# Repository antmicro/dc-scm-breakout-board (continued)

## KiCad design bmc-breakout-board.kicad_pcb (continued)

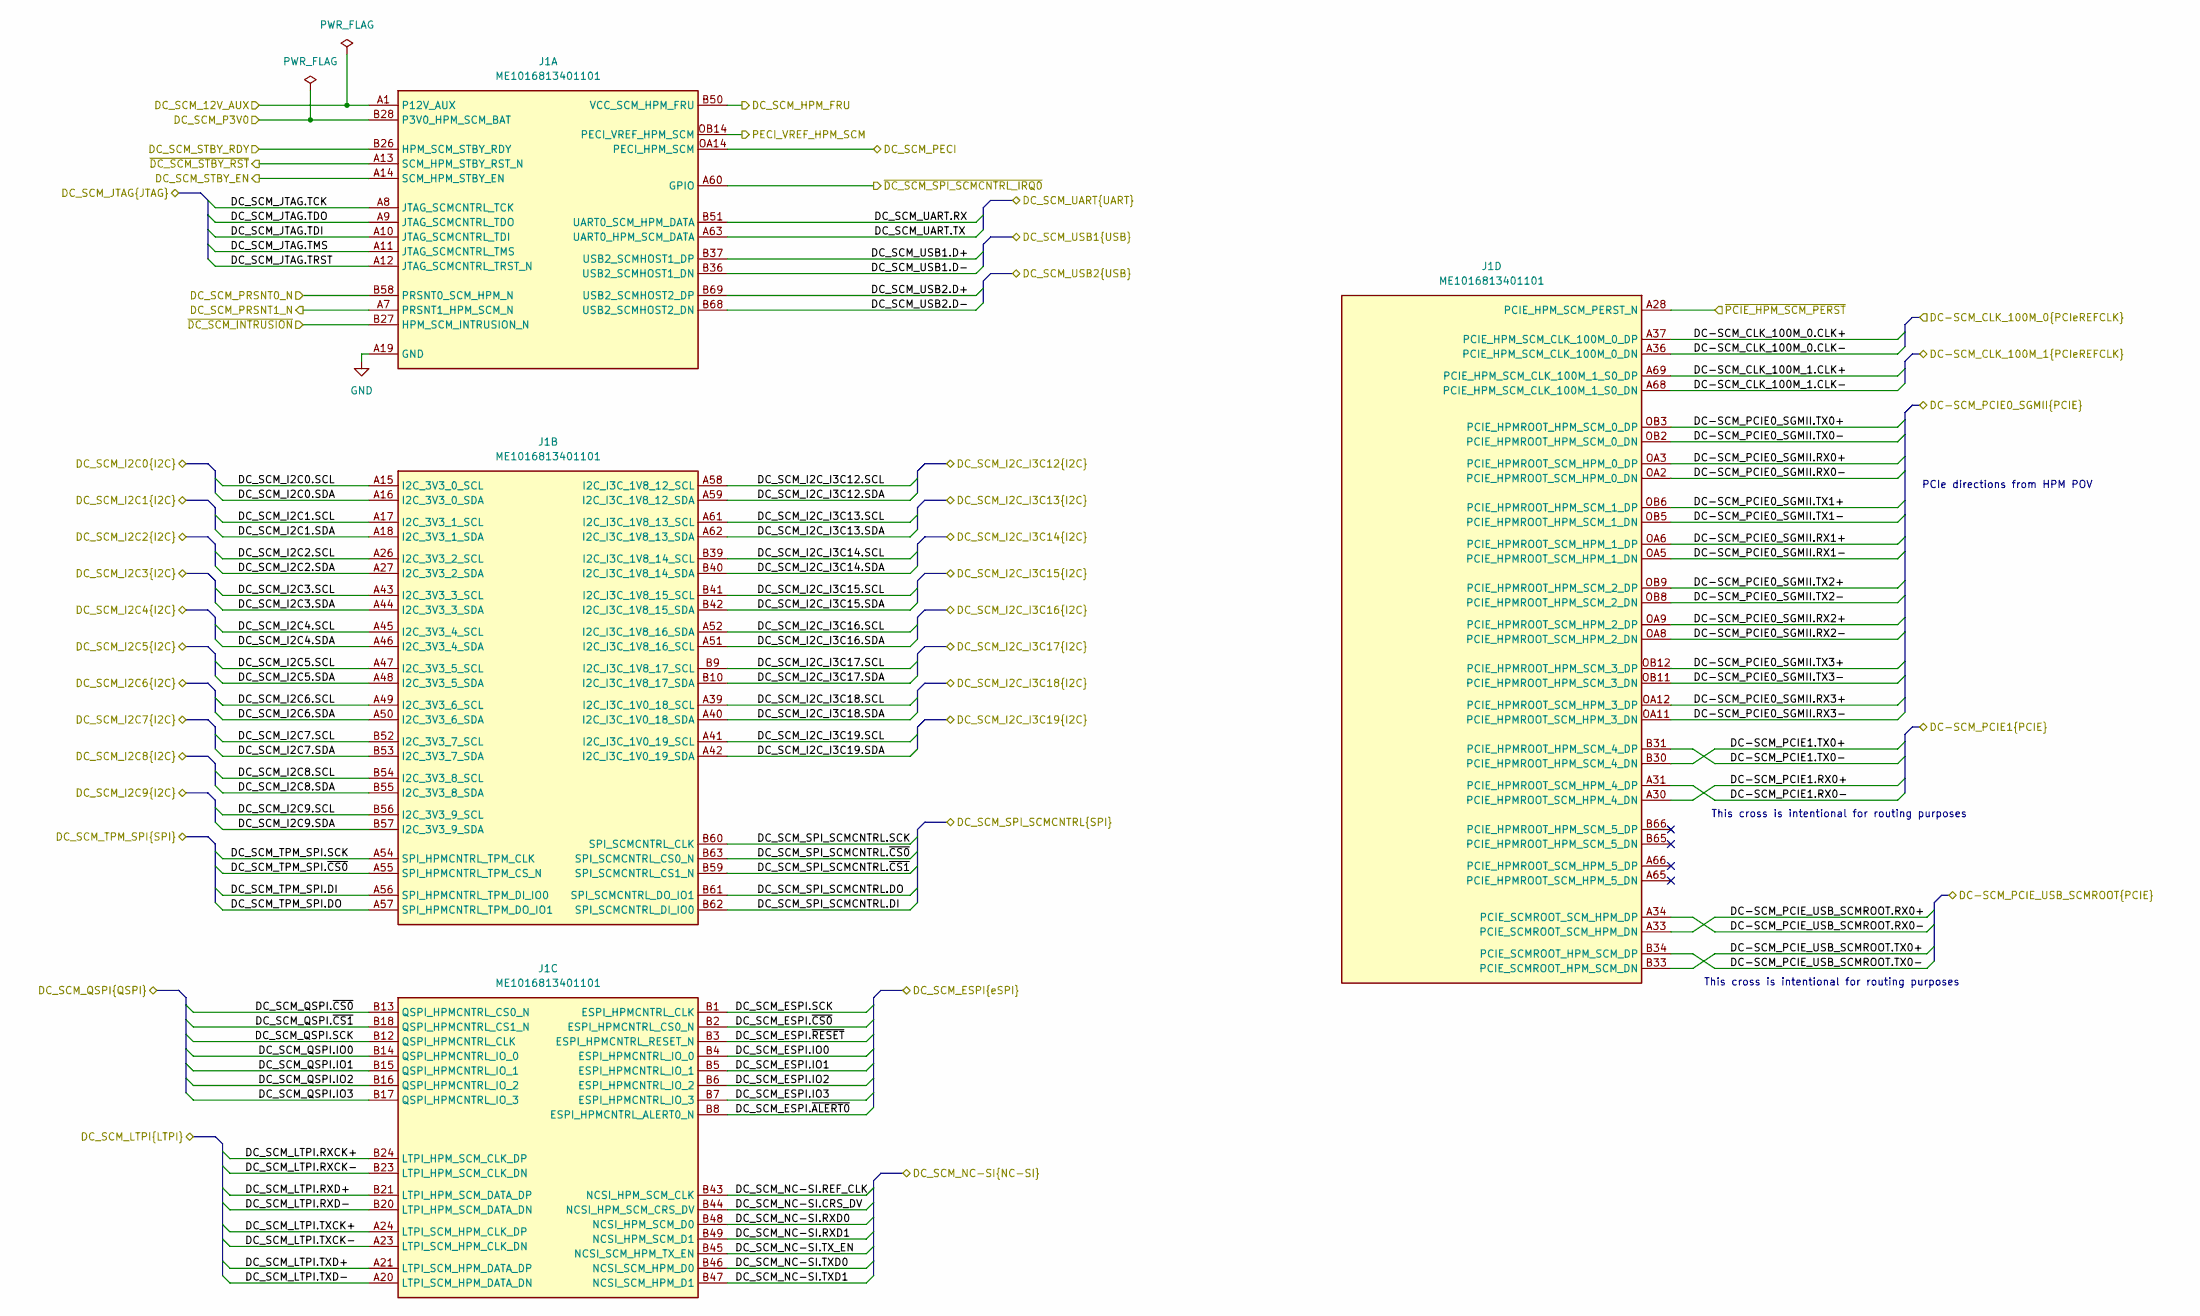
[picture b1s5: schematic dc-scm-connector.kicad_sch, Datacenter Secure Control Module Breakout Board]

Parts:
J1: Socket_DC-SCM-2.1_2x84_Rev-1-1_CUSTOM; Socket_DC-SCM-2.1_2x84_Rev-1-1; MPN ME1016813401101

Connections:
+12V: J1.A1 (P12V_AUX), J1.A2 (P12V_AUX), J1.A3 (P12V_AUX), J1.A4 (P12V_AUX); also elsewhere on the board
/DC-SCM 2.1 connector/DC-SCM_CLK_100M_0.CLK+: J1.A37 (PCIE_HPM_SCM_CLK_100M_0_DP); also elsewhere on the board
/DC-SCM 2.1 connector/DC-SCM_CLK_100M_0.CLK-: J1.A36 (PCIE_HPM_SCM_CLK_100M_0_DN); also elsewhere on the board
/DC-SCM 2.1 connector/DC-SCM_CLK_100M_1.CLK+: J1.A69 (PCIE_HPM_SCM_CLK_100M_1_S0_DP); also elsewhere on the board
/DC-SCM 2.1 connector/DC-SCM_CLK_100M_1.CLK-: J1.A68 (PCIE_HPM_SCM_CLK_100M_1_S0_DN); also elsewhere on the board
/DC-SCM 2.1 connector/DC-SCM_PCIE0_SGMII.RX0+: J1.OA3 (PCIE_HPMROOT_SCM_HPM_0_DP)
/DC-SCM 2.1 connector/DC-SCM_PCIE0_SGMII.RX0-: J1.OA2 (PCIE_HPMROOT_SCM_HPM_0_DN)
/DC-SCM 2.1 connector/DC-SCM_PCIE0_SGMII.RX1+: J1.OA6 (PCIE_HPMROOT_SCM_HPM_1_DP)
/DC-SCM 2.1 connector/DC-SCM_PCIE0_SGMII.RX1-: J1.OA5 (PCIE_HPMROOT_SCM_HPM_1_DN)
/DC-SCM 2.1 connector/DC-SCM_PCIE0_SGMII.RX2+: J1.OA9 (PCIE_HPMROOT_SCM_HPM_2_DP)
/DC-SCM 2.1 connector/DC-SCM_PCIE0_SGMII.RX2-: J1.OA8 (PCIE_HPMROOT_SCM_HPM_2_DN)
/DC-SCM 2.1 connector/DC-SCM_PCIE0_SGMII.RX3+: J1.OA12 (PCIE_HPMROOT_SCM_HPM_3_DP)
/DC-SCM 2.1 connector/DC-SCM_PCIE0_SGMII.RX3-: J1.OA11 (PCIE_HPMROOT_SCM_HPM_3_DN)
/DC-SCM 2.1 connector/DC-SCM_PCIE0_SGMII.TX0+: J1.OB3 (PCIE_HPMROOT_HPM_SCM_0_DP)
/DC-SCM 2.1 connector/DC-SCM_PCIE0_SGMII.TX0-: J1.OB2 (PCIE_HPMROOT_HPM_SCM_0_DN)
/DC-SCM 2.1 connector/DC-SCM_PCIE0_SGMII.TX1+: J1.OB6 (PCIE_HPMROOT_HPM_SCM_1_DP)
/DC-SCM 2.1 connector/DC-SCM_PCIE0_SGMII.TX1-: J1.OB5 (PCIE_HPMROOT_HPM_SCM_1_DN)
/DC-SCM 2.1 connector/DC-SCM_PCIE0_SGMII.TX2+: J1.OB9 (PCIE_HPMROOT_HPM_SCM_2_DP)
/DC-SCM 2.1 connector/DC-SCM_PCIE0_SGMII.TX2-: J1.OB8 (PCIE_HPMROOT_HPM_SCM_2_DN)
/DC-SCM 2.1 connector/DC-SCM_PCIE0_SGMII.TX3+: J1.OB12 (PCIE_HPMROOT_HPM_SCM_3_DP)
/DC-SCM 2.1 connector/DC-SCM_PCIE0_SGMII.TX3-: J1.OB11 (PCIE_HPMROOT_HPM_SCM_3_DN)
/DC-SCM 2.1 connector/DC-SCM_PCIE1.RX0+: J1.A30 (PCIE_HPMROOT_SCM_HPM_4_DN); also elsewhere on the board
/DC-SCM 2.1 connector/DC-SCM_PCIE1.RX0-: J1.A31 (PCIE_HPMROOT_SCM_HPM_4_DP); also elsewhere on the board
/DC-SCM 2.1 connector/DC-SCM_PCIE1.TX0+: J1.B30 (PCIE_HPMROOT_HPM_SCM_4_DN); also elsewhere on the board
/DC-SCM 2.1 connector/DC-SCM_PCIE1.TX0-: J1.B31 (PCIE_HPMROOT_HPM_SCM_4_DP); also elsewhere on the board
/DC-SCM 2.1 connector/DC-SCM_PCIE_USB_SCMROOT.RX0+: J1.A33 (PCIE_SCMROOT_SCM_HPM_DN); also elsewhere on the board
/DC-SCM 2.1 connector/DC-SCM_PCIE_USB_SCMROOT.RX0-: J1.A34 (PCIE_SCMROOT_SCM_HPM_DP); also elsewhere on the board
/DC-SCM 2.1 connector/DC-SCM_PCIE_USB_SCMROOT.TX0+: J1.B33 (PCIE_SCMROOT_HPM_SCM_DN); also elsewhere on the board
/DC-SCM 2.1 connector/DC-SCM_PCIE_USB_SCMROOT.TX0-: J1.B34 (PCIE_SCMROOT_HPM_SCM_DP); also elsewhere on the board
/DC-SCM 2.1 connector/DC_SCM_ESPI.IO0: J1.B4 (ESPI_HPMCNTRL_IO_0); also elsewhere on the board
/DC-SCM 2.1 connector/DC_SCM_ESPI.IO1: J1.B5 (ESPI_HPMCNTRL_IO_1); also elsewhere on the board
/DC-SCM 2.1 connector/DC_SCM_ESPI.IO2: J1.B6 (ESPI_HPMCNTRL_IO_2); also elsewhere on the board
/DC-SCM 2.1 connector/DC_SCM_ESPI.IO3: J1.B7 (ESPI_HPMCNTRL_IO_3); also elsewhere on the board
/DC-SCM 2.1 connector/DC_SCM_ESPI.SCK: J1.B1 (ESPI_HPMCNTRL_CLK); also elsewhere on the board
/DC-SCM 2.1 connector/DC_SCM_ESPI.~ALERT0: J1.B8 (ESPI_HPMCNTRL_ALERT0_N); also elsewhere on the board
/DC-SCM 2.1 connector/DC_SCM_ESPI.~CS0: J1.B2 (ESPI_HPMCNTRL_CS0_N); also elsewhere on the board
/DC-SCM 2.1 connector/DC_SCM_ESPI.~RESET: J1.B3 (ESPI_HPMCNTRL_RESET_N); also elsewhere on the board
/DC-SCM 2.1 connector/DC_SCM_HPM_FRU: J1.B50 (VCC_SCM_HPM_FRU); also elsewhere on the board
/DC-SCM 2.1 connector/DC_SCM_I2C0.SCL: J1.A15 (I2C_3V3_0_SCL); also elsewhere on the board
/DC-SCM 2.1 connector/DC_SCM_I2C0.SDA: J1.A16 (I2C_3V3_0_SDA); also elsewhere on the board
/DC-SCM 2.1 connector/DC_SCM_I2C1.SCL: J1.A17 (I2C_3V3_1_SCL); also elsewhere on the board
/DC-SCM 2.1 connector/DC_SCM_I2C1.SDA: J1.A18 (I2C_3V3_1_SDA); also elsewhere on the board
/DC-SCM 2.1 connector/DC_SCM_I2C2.SCL: J1.A26 (I2C_3V3_2_SCL); also elsewhere on the board
/DC-SCM 2.1 connector/DC_SCM_I2C2.SDA: J1.A27 (I2C_3V3_2_SDA); also elsewhere on the board
/DC-SCM 2.1 connector/DC_SCM_I2C3.SCL: J1.A43 (I2C_3V3_3_SCL); also elsewhere on the board
/DC-SCM 2.1 connector/DC_SCM_I2C3.SDA: J1.A44 (I2C_3V3_3_SDA); also elsewhere on the board
/DC-SCM 2.1 connector/DC_SCM_I2C4.SCL: J1.A45 (I2C_3V3_4_SCL); also elsewhere on the board
/DC-SCM 2.1 connector/DC_SCM_I2C4.SDA: J1.A46 (I2C_3V3_4_SDA); also elsewhere on the board
/DC-SCM 2.1 connector/DC_SCM_I2C5.SCL: J1.A47 (I2C_3V3_5_SCL); also elsewhere on the board
/DC-SCM 2.1 connector/DC_SCM_I2C5.SDA: J1.A48 (I2C_3V3_5_SDA); also elsewhere on the board
/DC-SCM 2.1 connector/DC_SCM_I2C6.SCL: J1.A49 (I2C_3V3_6_SCL); also elsewhere on the board
/DC-SCM 2.1 connector/DC_SCM_I2C6.SDA: J1.A50 (I2C_3V3_6_SDA); also elsewhere on the board
/DC-SCM 2.1 connector/DC_SCM_I2C7.SCL: J1.B52 (I2C_3V3_7_SCL); also elsewhere on the board
/DC-SCM 2.1 connector/DC_SCM_I2C7.SDA: J1.B53 (I2C_3V3_7_SDA); also elsewhere on the board
/DC-SCM 2.1 connector/DC_SCM_I2C8.SCL: J1.B54 (I2C_3V3_8_SCL); also elsewhere on the board
/DC-SCM 2.1 connector/DC_SCM_I2C8.SDA: J1.B55 (I2C_3V3_8_SDA); also elsewhere on the board
/DC-SCM 2.1 connector/DC_SCM_I2C9.SCL: J1.B56 (I2C_3V3_9_SCL); also elsewhere on the board
/DC-SCM 2.1 connector/DC_SCM_I2C9.SDA: J1.B57 (I2C_3V3_9_SDA); also elsewhere on the board
/DC-SCM 2.1 connector/DC_SCM_I2C_I3C12.SCL: J1.A58 (I2C_I3C_1V8_12_SCL); also elsewhere on the board
/DC-SCM 2.1 connector/DC_SCM_I2C_I3C12.SDA: J1.A59 (I2C_I3C_1V8_12_SDA); also elsewhere on the board
/DC-SCM 2.1 connector/DC_SCM_I2C_I3C13.SCL: J1.A61 (I2C_I3C_1V8_13_SCL); also elsewhere on the board
/DC-SCM 2.1 connector/DC_SCM_I2C_I3C13.SDA: J1.A62 (I2C_I3C_1V8_13_SDA); also elsewhere on the board
/DC-SCM 2.1 connector/DC_SCM_I2C_I3C14.SCL: J1.B39 (I2C_I3C_1V8_14_SCL); also elsewhere on the board
/DC-SCM 2.1 connector/DC_SCM_I2C_I3C14.SDA: J1.B40 (I2C_I3C_1V8_14_SDA); also elsewhere on the board
/DC-SCM 2.1 connector/DC_SCM_I2C_I3C15.SCL: J1.B41 (I2C_I3C_1V8_15_SCL); also elsewhere on the board
/DC-SCM 2.1 connector/DC_SCM_I2C_I3C15.SDA: J1.B42 (I2C_I3C_1V8_15_SDA); also elsewhere on the board
/DC-SCM 2.1 connector/DC_SCM_I2C_I3C16.SCL: J1.A52 (I2C_I3C_1V8_16_SDA); also elsewhere on the board
/DC-SCM 2.1 connector/DC_SCM_I2C_I3C16.SDA: J1.A51 (I2C_I3C_1V8_16_SCL); also elsewhere on the board
/DC-SCM 2.1 connector/DC_SCM_I2C_I3C17.SCL: J1.B9 (I2C_I3C_1V8_17_SCL); also elsewhere on the board
/DC-SCM 2.1 connector/DC_SCM_I2C_I3C17.SDA: J1.B10 (I2C_I3C_1V8_17_SDA); also elsewhere on the board
/DC-SCM 2.1 connector/DC_SCM_I2C_I3C18.SCL: J1.A39 (I2C_I3C_1V0_18_SCL); also elsewhere on the board
/DC-SCM 2.1 connector/DC_SCM_I2C_I3C18.SDA: J1.A40 (I2C_I3C_1V0_18_SDA); also elsewhere on the board
/DC-SCM 2.1 connector/DC_SCM_I2C_I3C19.SCL: J1.A41 (I2C_I3C_1V0_19_SCL); also elsewhere on the board
/DC-SCM 2.1 connector/DC_SCM_I2C_I3C19.SDA: J1.A42 (I2C_I3C_1V0_19_SDA); also elsewhere on the board
/DC-SCM 2.1 connector/DC_SCM_JTAG.TCK: J1.A8 (JTAG_SCMCNTRL_TCK); also elsewhere on the board
/DC-SCM 2.1 connector/DC_SCM_JTAG.TDI: J1.A10 (JTAG_SCMCNTRL_TDI); also elsewhere on the board
/DC-SCM 2.1 connector/DC_SCM_JTAG.TDO: J1.A9 (JTAG_SCMCNTRL_TDO); also elsewhere on the board
/DC-SCM 2.1 connector/DC_SCM_JTAG.TMS: J1.A11 (JTAG_SCMCNTRL_TMS); also elsewhere on the board
/DC-SCM 2.1 connector/DC_SCM_JTAG.TRST: J1.A12 (JTAG_SCMCNTRL_TRST_N); also elsewhere on the board
/DC-SCM 2.1 connector/DC_SCM_LTPI.RXCK+: J1.B24 (LTPI_HPM_SCM_CLK_DP); also elsewhere on the board
/DC-SCM 2.1 connector/DC_SCM_LTPI.RXCK-: J1.B23 (LTPI_HPM_SCM_CLK_DN); also elsewhere on the board
/DC-SCM 2.1 connector/DC_SCM_LTPI.RXD+: J1.B21 (LTPI_HPM_SCM_DATA_DP); also elsewhere on the board
/DC-SCM 2.1 connector/DC_SCM_LTPI.RXD-: J1.B20 (LTPI_HPM_SCM_DATA_DN); also elsewhere on the board
/DC-SCM 2.1 connector/DC_SCM_LTPI.TXCK+: J1.A24 (LTPI_SCM_HPM_CLK_DP); also elsewhere on the board
/DC-SCM 2.1 connector/DC_SCM_LTPI.TXCK-: J1.A23 (LTPI_SCM_HPM_CLK_DN); also elsewhere on the board
/DC-SCM 2.1 connector/DC_SCM_LTPI.TXD+: J1.A21 (LTPI_SCM_HPM_DATA_DP); also elsewhere on the board
/DC-SCM 2.1 connector/DC_SCM_LTPI.TXD-: J1.A20 (LTPI_SCM_HPM_DATA_DN); also elsewhere on the board
/DC-SCM 2.1 connector/DC_SCM_NC-SI.CRS_DV: J1.B44 (NCSI_HPM_SCM_CRS_DV); also elsewhere on the board
/DC-SCM 2.1 connector/DC_SCM_NC-SI.REF_CLK: J1.B43 (NCSI_HPM_SCM_CLK); also elsewhere on the board
/DC-SCM 2.1 connector/DC_SCM_NC-SI.RXD0: J1.B48 (NCSI_HPM_SCM_D0); also elsewhere on the board
/DC-SCM 2.1 connector/DC_SCM_NC-SI.RXD1: J1.B49 (NCSI_HPM_SCM_D1); also elsewhere on the board
/DC-SCM 2.1 connector/DC_SCM_NC-SI.TXD0: J1.B46 (NCSI_SCM_HPM_D0); also elsewhere on the board
/DC-SCM 2.1 connector/DC_SCM_NC-SI.TXD1: J1.B47 (NCSI_SCM_HPM_D1); also elsewhere on the board
/DC-SCM 2.1 connector/DC_SCM_NC-SI.TX_EN: J1.B45 (NCSI_SCM_HPM_TX_EN); also elsewhere on the board
/DC-SCM 2.1 connector/DC_SCM_P3V0: J1.B28 (P3V0_HPM_SCM_BAT); also elsewhere on the board
/DC-SCM 2.1 connector/DC_SCM_PECI: J1.OA14 (PECI_HPM_SCM); also elsewhere on the board
/DC-SCM 2.1 connector/DC_SCM_PRSNT0_N: J1.B58 (PRSNT0_SCM_HPM_N); also elsewhere on the board
/DC-SCM 2.1 connector/DC_SCM_PRSNT1_N: J1.A7 (PRSNT1_HPM_SCM_N); also elsewhere on the board
/DC-SCM 2.1 connector/DC_SCM_QSPI.IO0: J1.B14 (QSPI_HPMCNTRL_IO_0); also elsewhere on the board
/DC-SCM 2.1 connector/DC_SCM_QSPI.IO1: J1.B15 (QSPI_HPMCNTRL_IO_1); also elsewhere on the board
/DC-SCM 2.1 connector/DC_SCM_QSPI.IO2: J1.B16 (QSPI_HPMCNTRL_IO_2); also elsewhere on the board
/DC-SCM 2.1 connector/DC_SCM_QSPI.IO3: J1.B17 (QSPI_HPMCNTRL_IO_3); also elsewhere on the board
/DC-SCM 2.1 connector/DC_SCM_QSPI.SCK: J1.B12 (QSPI_HPMCNTRL_CLK); also elsewhere on the board
/DC-SCM 2.1 connector/DC_SCM_QSPI.~CS0: J1.B13 (QSPI_HPMCNTRL_CS0_N); also elsewhere on the board
/DC-SCM 2.1 connector/DC_SCM_QSPI.~CS1: J1.B18 (QSPI_HPMCNTRL_CS1_N); also elsewhere on the board
/DC-SCM 2.1 connector/DC_SCM_SPI_SCMCNTRL.DI: J1.B62 (SPI_SCMCNTRL_DI_IO0); also elsewhere on the board
/DC-SCM 2.1 connector/DC_SCM_SPI_SCMCNTRL.DO: J1.B61 (SPI_SCMCNTRL_DO_IO1); also elsewhere on the board
/DC-SCM 2.1 connector/DC_SCM_SPI_SCMCNTRL.SCK: J1.B60 (SPI_SCMCNTRL_CLK); also elsewhere on the board
/DC-SCM 2.1 connector/DC_SCM_SPI_SCMCNTRL.~CS0: J1.B63 (SPI_SCMCNTRL_CS0_N); also elsewhere on the board
/DC-SCM 2.1 connector/DC_SCM_SPI_SCMCNTRL.~CS1: J1.B59 (SPI_SCMCNTRL_CS1_N); also elsewhere on the board
/DC-SCM 2.1 connector/DC_SCM_STBY_EN: J1.A14 (SCM_HPM_STBY_EN); also elsewhere on the board
/DC-SCM 2.1 connector/DC_SCM_STBY_RDY: J1.B26 (HPM_SCM_STBY_RDY); also elsewhere on the board
/DC-SCM 2.1 connector/DC_SCM_TPM_SPI.DI: J1.A56 (SPI_HPMCNTRL_TPM_DI_IO0); also elsewhere on the board
/DC-SCM 2.1 connector/DC_SCM_TPM_SPI.DO: J1.A57 (SPI_HPMCNTRL_TPM_DO_IO1); also elsewhere on the board
/DC-SCM 2.1 connector/DC_SCM_TPM_SPI.SCK: J1.A54 (SPI_HPMCNTRL_TPM_CLK); also elsewhere on the board
/DC-SCM 2.1 connector/DC_SCM_TPM_SPI.~CS0: J1.A55 (SPI_HPMCNTRL_TPM_CS_N); also elsewhere on the board
/DC-SCM 2.1 connector/DC_SCM_UART.RX: J1.B51 (UART0_SCM_HPM_DATA); also elsewhere on the board
/DC-SCM 2.1 connector/DC_SCM_UART.TX: J1.A63 (UART0_HPM_SCM_DATA); also elsewhere on the board
/DC-SCM 2.1 connector/DC_SCM_USB1.D+: J1.B37 (USB2_SCMHOST1_DP); also elsewhere on the board
/DC-SCM 2.1 connector/DC_SCM_USB1.D-: J1.B36 (USB2_SCMHOST1_DN); also elsewhere on the board
/DC-SCM 2.1 connector/DC_SCM_USB2.D+: J1.B69 (USB2_SCMHOST2_DP); also elsewhere on the board
/DC-SCM 2.1 connector/DC_SCM_USB2.D-: J1.B68 (USB2_SCMHOST2_DN); also elsewhere on the board
/DC-SCM 2.1 connector/PECI_VREF_HPM_SCM: J1.OB14 (PECI_VREF_HPM_SCM); also elsewhere on the board
/DC-SCM 2.1 connector/~DC_SCM_INTRUSION: J1.B27 (HPM_SCM_INTRUSION_N); also elsewhere on the board
/DC-SCM 2.1 connector/~DC_SCM_SPI_SCMCNTRL_IRQ0: J1.A60 (GPIO); also elsewhere on the board
/DC-SCM 2.1 connector/~DC_SCM_STBY_RST: J1.A13 (SCM_HPM_STBY_RST_N); also elsewhere on the board
/DC-SCM 2.1 connector/~PCIE_HPM_SCM_PERST: J1.A28 (PCIE_HPM_SCM_PERST_N); also elsewhere on the board
GND: J1.A5 (GND), J1.A6 (GND), J1.A19 (GND), J1.A22 (GND), J1.A25 (GND), J1.A29 (GND), J1.A32 (GND), J1.A35 (GND), J1.A38 (GND), J1.A53 (GND), J1.A64 (GND), J1.A67 (GND), J1.A70 (GND), J1.B11 (GND), J1.B19 (GND), J1.B22 (GND), J1.B25 (GND), J1.B29 (GND), J1.B32 (GND), J1.B35 (GND), J1.B38 (GND), J1.B64 (GND), J1.B67 (GND), J1.B70 (GND), J1.OA1 (GND), J1.OA4 (GND), J1.OA7 (GND), J1.OA10 (GND), J1.OA13 (GND), J1.OB1 (GND), J1.OB4 (GND), J1.OB7 (GND), J1.OB10 (GND), J1.OB13 (GND); also elsewhere on the board

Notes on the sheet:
PCIe directions from HPM POV
This cross is intentional for routing purposes

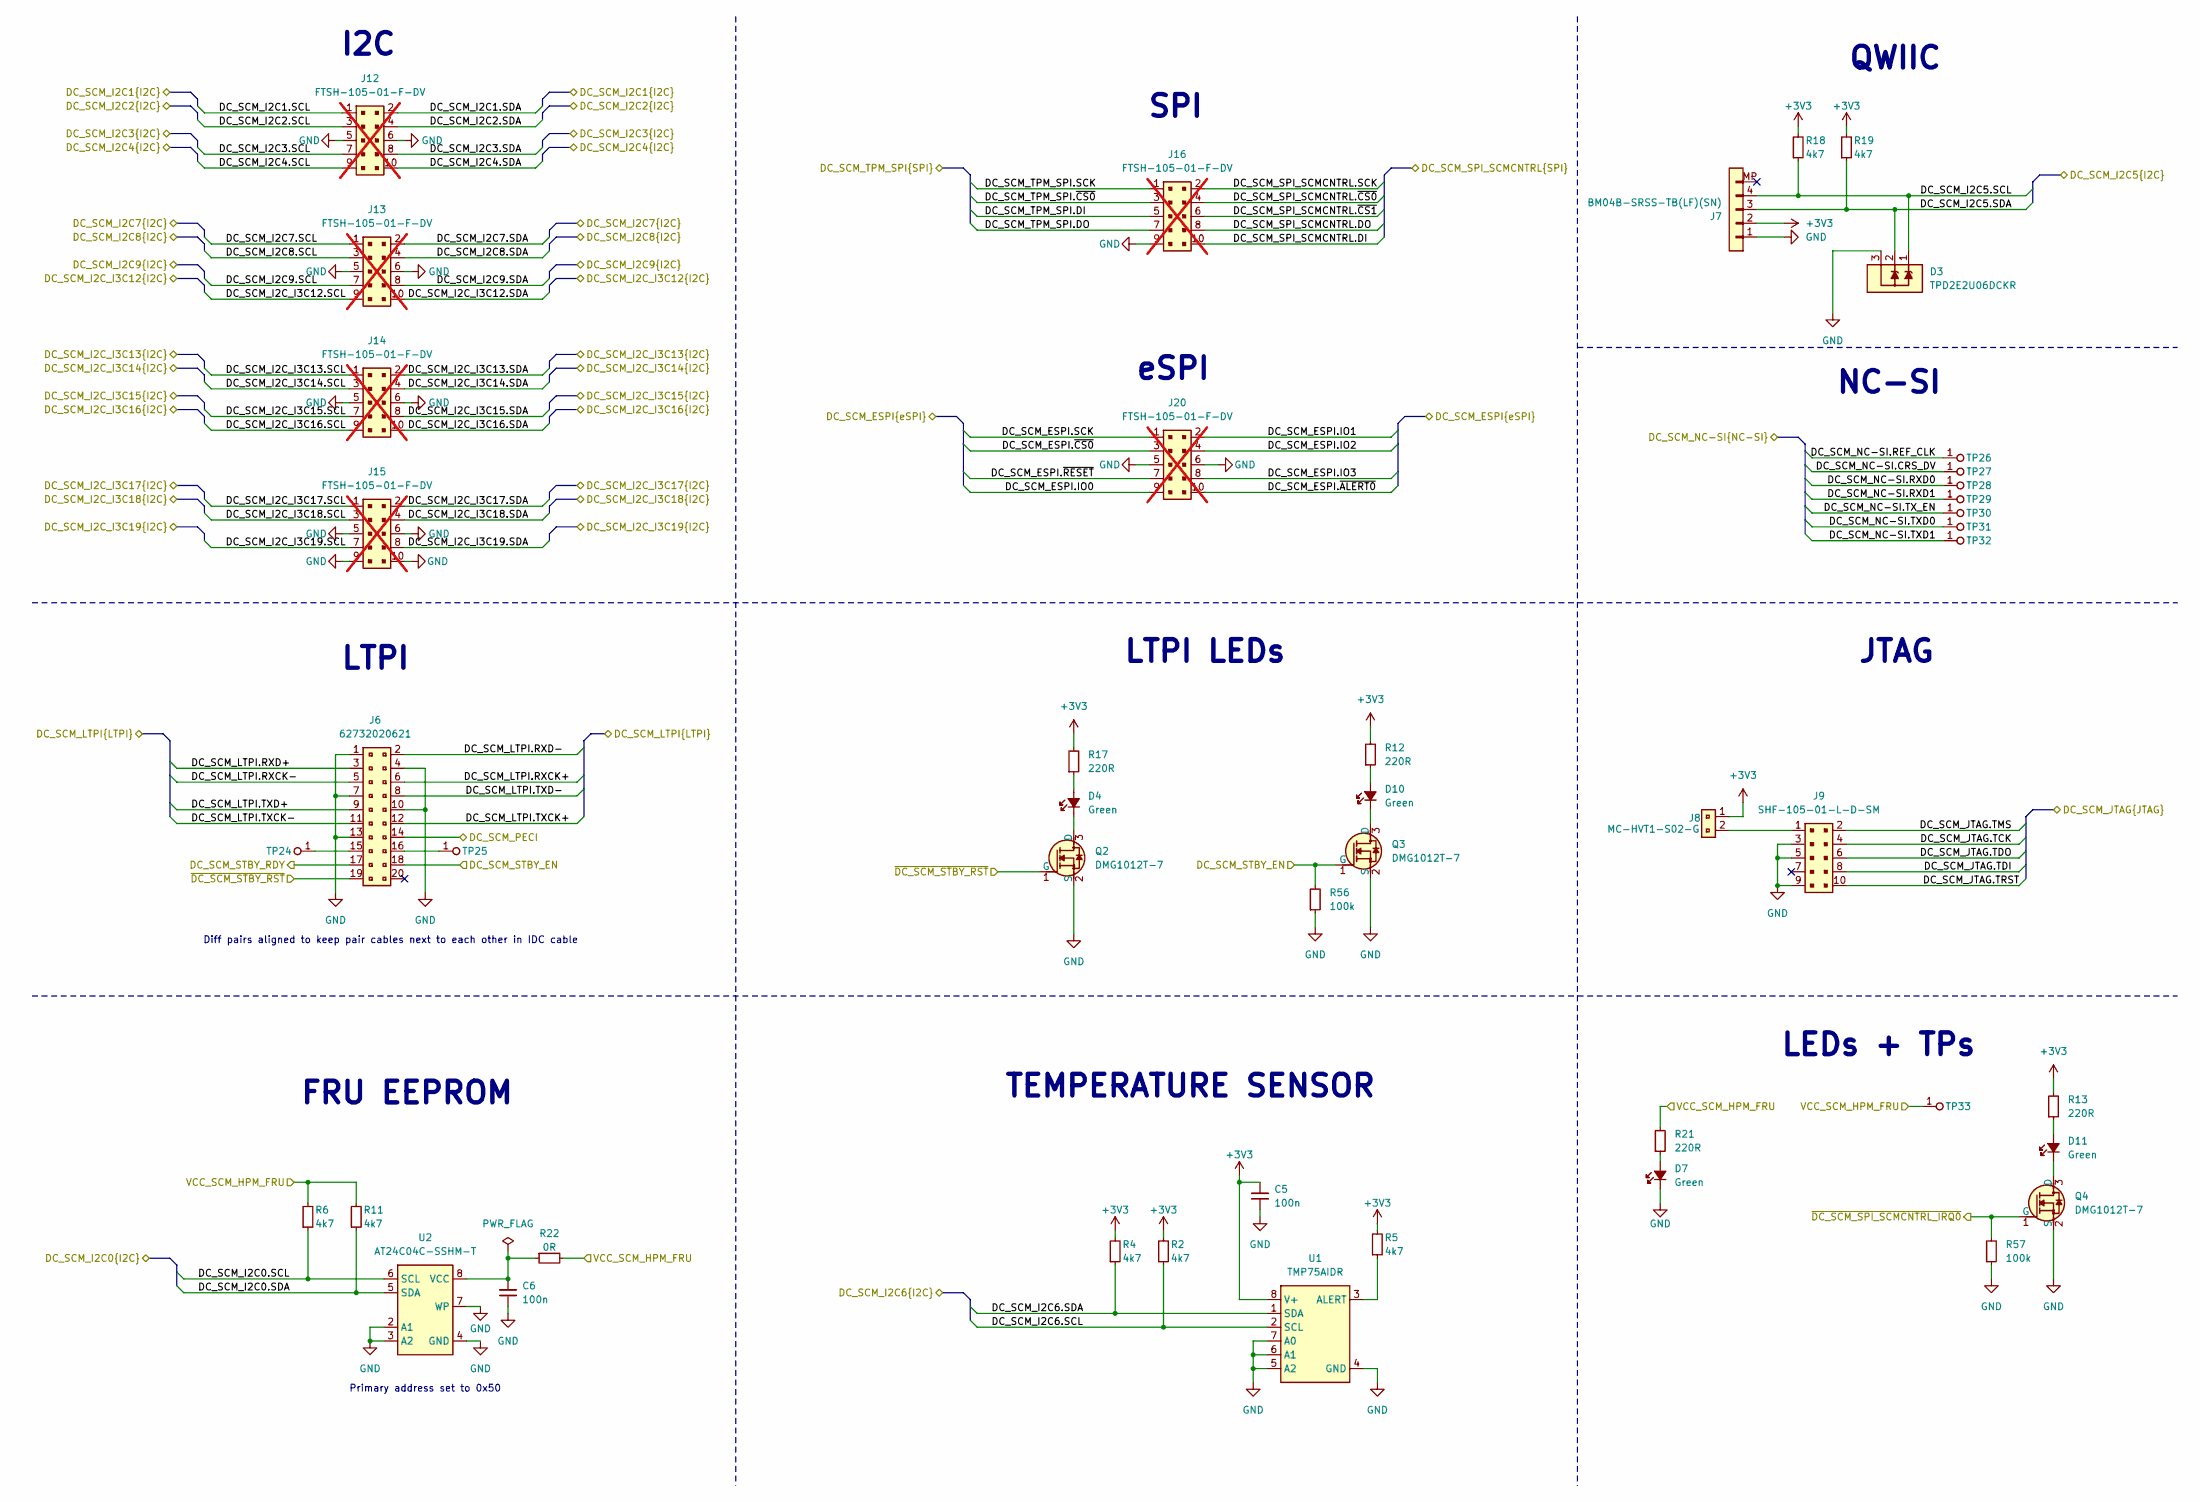
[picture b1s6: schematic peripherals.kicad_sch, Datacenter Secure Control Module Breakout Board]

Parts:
C5, C6: C_100n_0402; C_0402_1005Metric; Voltage 50V; MPN GRM155R61H104KE14D
D3: TPD2E2U06_SC70; SC70-3; MPN TPD2E2U06DCKR
D4, D7, D10, D11: LED_G_0402_VLMTG1500-GS08; LED_0402_1005Metric_G; MPN VLMTG1500-GS08
J6: PinHeader_2x10_P1.27mm_SMD_Shrouded; MPN 62732020621
J7: JST_SH_1x4_BM04B-SRSS-TB-LF-SN; Conn_JST_SH_1x4_BM04B-SRSS-TB-LF-SN; MPN BM04B-SRSS-TB(LF)(SN)
J8: PinHeader_1x2_P1.27mm_Drill0.7mm; MPN MC-HVT1-S02-G
J9: PinHeader_2x5_P1.27mm_SMD_Shrouded; MPN SHF-105-01-L-D-SM
J12, J13, J14, J15, J16, J20: PinHeader_2x5_P1.27mm_SMD; MPN FTSH-105-01-F-DV; not fitted
Q2, Q3, Q4: DMG1012T-7; SOT-523; MPN DMG1012T-7
R2, R4, R5, R6, R11, R18, R19: R_4k7_0402; R_0402_1005Metric; Tolerance 1%; MPN CR0402-FX-4701GLF
R12, R13, R17, R21: R_220R_0402; R_0402_1005Metric; Tolerance 1%; MPN CR0402-FX-2200GLF
R22: R_0R_0402; R_0402_1005Metric; MPN ERJ2GE0R00X
R56, R57: R_100k_0402; R_0402_1005Metric; Tolerance 1%; MPN CR0402-FX-1003GLF
TP24, TP25, TP26, TP27, TP28, TP29, TP30, TP31, TP32, TP33: TP_1.5mm_SMD; TP_SMD_1.5mm
U1: TMP75AIDR; SOIC-8_3.9x4.9x1.75mm_P1.27mm; MPN TMP75AIDR
U2: AT24C04C_SOIC8; SOIC-8_3.9x4.9x1.75mm_P1.27mm; MPN AT24C04C-SSHM-T

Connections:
+3V3: C5.2, J7.2, J8.1, R2.2, R4.2, R5.2, R12.2, R13.2, R17.2, R18.2, R19.2, U1.8 (V+); also elsewhere on the board
/DC-SCM 2.1 connector/DC_SCM_ESPI.IO0: J20.9; also elsewhere on the board
/DC-SCM 2.1 connector/DC_SCM_ESPI.IO1: J20.2; also elsewhere on the board
/DC-SCM 2.1 connector/DC_SCM_ESPI.IO2: J20.4; also elsewhere on the board
/DC-SCM 2.1 connector/DC_SCM_ESPI.IO3: J20.8; also elsewhere on the board
/DC-SCM 2.1 connector/DC_SCM_ESPI.SCK: J20.1; also elsewhere on the board
/DC-SCM 2.1 connector/DC_SCM_ESPI.~ALERT0: J20.10; also elsewhere on the board
/DC-SCM 2.1 connector/DC_SCM_ESPI.~CS0: J20.3; also elsewhere on the board
/DC-SCM 2.1 connector/DC_SCM_ESPI.~RESET: J20.7; also elsewhere on the board
/DC-SCM 2.1 connector/DC_SCM_HPM_FRU: R6.2, R11.2, R21.2, R22.2, TP33.1; also elsewhere on the board
/DC-SCM 2.1 connector/DC_SCM_I2C0.SCL: R6.1, U2.6 (SCL); also elsewhere on the board
/DC-SCM 2.1 connector/DC_SCM_I2C0.SDA: R11.1, U2.5 (SDA); also elsewhere on the board
/DC-SCM 2.1 connector/DC_SCM_I2C1.SCL: J12.1; also elsewhere on the board
/DC-SCM 2.1 connector/DC_SCM_I2C1.SDA: J12.2; also elsewhere on the board
/DC-SCM 2.1 connector/DC_SCM_I2C2.SCL: J12.3; also elsewhere on the board
/DC-SCM 2.1 connector/DC_SCM_I2C2.SDA: J12.4; also elsewhere on the board
/DC-SCM 2.1 connector/DC_SCM_I2C3.SCL: J12.7; also elsewhere on the board
/DC-SCM 2.1 connector/DC_SCM_I2C3.SDA: J12.8; also elsewhere on the board
/DC-SCM 2.1 connector/DC_SCM_I2C4.SCL: J12.9; also elsewhere on the board
/DC-SCM 2.1 connector/DC_SCM_I2C4.SDA: J12.10; also elsewhere on the board
/DC-SCM 2.1 connector/DC_SCM_I2C5.SCL: D3.1, J7.4, R18.1; also elsewhere on the board
/DC-SCM 2.1 connector/DC_SCM_I2C5.SDA: D3.2, J7.3, R19.1; also elsewhere on the board
/DC-SCM 2.1 connector/DC_SCM_I2C6.SCL: R2.1, U1.2 (SCL); also elsewhere on the board
/DC-SCM 2.1 connector/DC_SCM_I2C6.SDA: R4.1, U1.1 (SDA); also elsewhere on the board
/DC-SCM 2.1 connector/DC_SCM_I2C7.SCL: J13.1; also elsewhere on the board
/DC-SCM 2.1 connector/DC_SCM_I2C7.SDA: J13.2; also elsewhere on the board
/DC-SCM 2.1 connector/DC_SCM_I2C8.SCL: J13.3; also elsewhere on the board
/DC-SCM 2.1 connector/DC_SCM_I2C8.SDA: J13.4; also elsewhere on the board
/DC-SCM 2.1 connector/DC_SCM_I2C9.SCL: J13.7; also elsewhere on the board
/DC-SCM 2.1 connector/DC_SCM_I2C9.SDA: J13.8; also elsewhere on the board
/DC-SCM 2.1 connector/DC_SCM_I2C_I3C12.SCL: J13.9; also elsewhere on the board
/DC-SCM 2.1 connector/DC_SCM_I2C_I3C12.SDA: J13.10; also elsewhere on the board
/DC-SCM 2.1 connector/DC_SCM_I2C_I3C13.SCL: J14.1; also elsewhere on the board
/DC-SCM 2.1 connector/DC_SCM_I2C_I3C13.SDA: J14.2; also elsewhere on the board
/DC-SCM 2.1 connector/DC_SCM_I2C_I3C14.SCL: J14.3; also elsewhere on the board
/DC-SCM 2.1 connector/DC_SCM_I2C_I3C14.SDA: J14.4; also elsewhere on the board
/DC-SCM 2.1 connector/DC_SCM_I2C_I3C15.SCL: J14.7; also elsewhere on the board
/DC-SCM 2.1 connector/DC_SCM_I2C_I3C15.SDA: J14.8; also elsewhere on the board
/DC-SCM 2.1 connector/DC_SCM_I2C_I3C16.SCL: J14.9; also elsewhere on the board
/DC-SCM 2.1 connector/DC_SCM_I2C_I3C16.SDA: J14.10; also elsewhere on the board
/DC-SCM 2.1 connector/DC_SCM_I2C_I3C17.SCL: J15.1; also elsewhere on the board
/DC-SCM 2.1 connector/DC_SCM_I2C_I3C17.SDA: J15.2; also elsewhere on the board
/DC-SCM 2.1 connector/DC_SCM_I2C_I3C18.SCL: J15.3; also elsewhere on the board
/DC-SCM 2.1 connector/DC_SCM_I2C_I3C18.SDA: J15.4; also elsewhere on the board
/DC-SCM 2.1 connector/DC_SCM_I2C_I3C19.SCL: J15.7; also elsewhere on the board
/DC-SCM 2.1 connector/DC_SCM_I2C_I3C19.SDA: J15.8; also elsewhere on the board
/DC-SCM 2.1 connector/DC_SCM_JTAG.TCK: J9.4; also elsewhere on the board
/DC-SCM 2.1 connector/DC_SCM_JTAG.TDI: J9.8; also elsewhere on the board
/DC-SCM 2.1 connector/DC_SCM_JTAG.TDO: J9.6; also elsewhere on the board
/DC-SCM 2.1 connector/DC_SCM_JTAG.TMS: J9.2; also elsewhere on the board
/DC-SCM 2.1 connector/DC_SCM_JTAG.TRST: J9.10; also elsewhere on the board
/DC-SCM 2.1 connector/DC_SCM_LTPI.RXCK+: J6.6; also elsewhere on the board
/DC-SCM 2.1 connector/DC_SCM_LTPI.RXCK-: J6.5; also elsewhere on the board
/DC-SCM 2.1 connector/DC_SCM_LTPI.RXD+: J6.3; also elsewhere on the board
/DC-SCM 2.1 connector/DC_SCM_LTPI.RXD-: J6.2; also elsewhere on the board
/DC-SCM 2.1 connector/DC_SCM_LTPI.TXCK+: J6.12; also elsewhere on the board
/DC-SCM 2.1 connector/DC_SCM_LTPI.TXCK-: J6.11; also elsewhere on the board
/DC-SCM 2.1 connector/DC_SCM_LTPI.TXD+: J6.9; also elsewhere on the board
/DC-SCM 2.1 connector/DC_SCM_LTPI.TXD-: J6.8; also elsewhere on the board
/DC-SCM 2.1 connector/DC_SCM_NC-SI.CRS_DV: TP27.1; also elsewhere on the board
/DC-SCM 2.1 connector/DC_SCM_NC-SI.REF_CLK: TP26.1; also elsewhere on the board
/DC-SCM 2.1 connector/DC_SCM_NC-SI.RXD0: TP28.1; also elsewhere on the board
/DC-SCM 2.1 connector/DC_SCM_NC-SI.RXD1: TP29.1; also elsewhere on the board
/DC-SCM 2.1 connector/DC_SCM_NC-SI.TXD0: TP31.1; also elsewhere on the board
/DC-SCM 2.1 connector/DC_SCM_NC-SI.TXD1: TP32.1; also elsewhere on the board
/DC-SCM 2.1 connector/DC_SCM_NC-SI.TX_EN: TP30.1; also elsewhere on the board
/DC-SCM 2.1 connector/DC_SCM_PECI: J6.14; also elsewhere on the board
/DC-SCM 2.1 connector/DC_SCM_SPI_SCMCNTRL.DI: J16.10; also elsewhere on the board
/DC-SCM 2.1 connector/DC_SCM_SPI_SCMCNTRL.DO: J16.8; also elsewhere on the board
/DC-SCM 2.1 connector/DC_SCM_SPI_SCMCNTRL.SCK: J16.2; also elsewhere on the board
/DC-SCM 2.1 connector/DC_SCM_SPI_SCMCNTRL.~CS0: J16.4; also elsewhere on the board
/DC-SCM 2.1 connector/DC_SCM_SPI_SCMCNTRL.~CS1: J16.6; also elsewhere on the board
/DC-SCM 2.1 connector/DC_SCM_STBY_EN: J6.18, Q3.1 (G), R56.2; also elsewhere on the board
/DC-SCM 2.1 connector/DC_SCM_STBY_RDY: J6.17; also elsewhere on the board
/DC-SCM 2.1 connector/DC_SCM_TPM_SPI.DI: J16.5; also elsewhere on the board
/DC-SCM 2.1 connector/DC_SCM_TPM_SPI.DO: J16.7; also elsewhere on the board
/DC-SCM 2.1 connector/DC_SCM_TPM_SPI.SCK: J16.1; also elsewhere on the board
/DC-SCM 2.1 connector/DC_SCM_TPM_SPI.~CS0: J16.3; also elsewhere on the board
/DC-SCM 2.1 connector/~DC_SCM_SPI_SCMCNTRL_IRQ0: Q4.1 (G), R57.2; also elsewhere on the board
/DC-SCM 2.1 connector/~DC_SCM_STBY_RST: J6.19, Q2.1 (G); also elsewhere on the board
GND: C5.1, C6.1, D3.3, D7.1 (C), J6.1, J6.4, J6.7, J6.10, J6.13, J7.1, J9.3, J9.5, J9.9, J12.5, J12.6, J13.5, J13.6, J14.5, J14.6, J15.5, J15.6, J15.9, J15.10, J16.9, J20.5, J20.6, Q2.2 (S), Q3.2 (S), Q4.2 (S), R56.1, R57.1, U1.4 (GND), U1.5 (A2), U1.6 (A1), U1.7 (A0), U2.2 (A1), U2.3 (A2), U2.4 (GND), U2.7 (WP); also elsewhere on the board
unnamed: D4.2 (A), R17.1
unnamed: D4.1 (C), Q2.3 (D)
unnamed: D7.2 (A), R21.1
unnamed: D10.2 (A), R12.1
unnamed: D10.1 (C), Q3.3 (D)
unnamed: D11.2 (A), R13.1
unnamed: D11.1 (C), Q4.3 (D)
unnamed: J6.15, TP24.1
unnamed: J6.16, TP25.1
unnamed: J8.2, J9.1
unnamed: R5.1, U1.3 (ALERT)
unnamed: C6.2, R22.1, U2.8 (VCC)

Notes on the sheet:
FRU EEPROM
QWIIC
Primary address set to 0x50
NC-SI
I2C
LEDs + TPs
Diff pairs aligned to keep pair cables next to each other in IDC cable
TEMPERATURE SENSOR
SPI
eSPI
LTPI
LTPI LEDs
JTAG

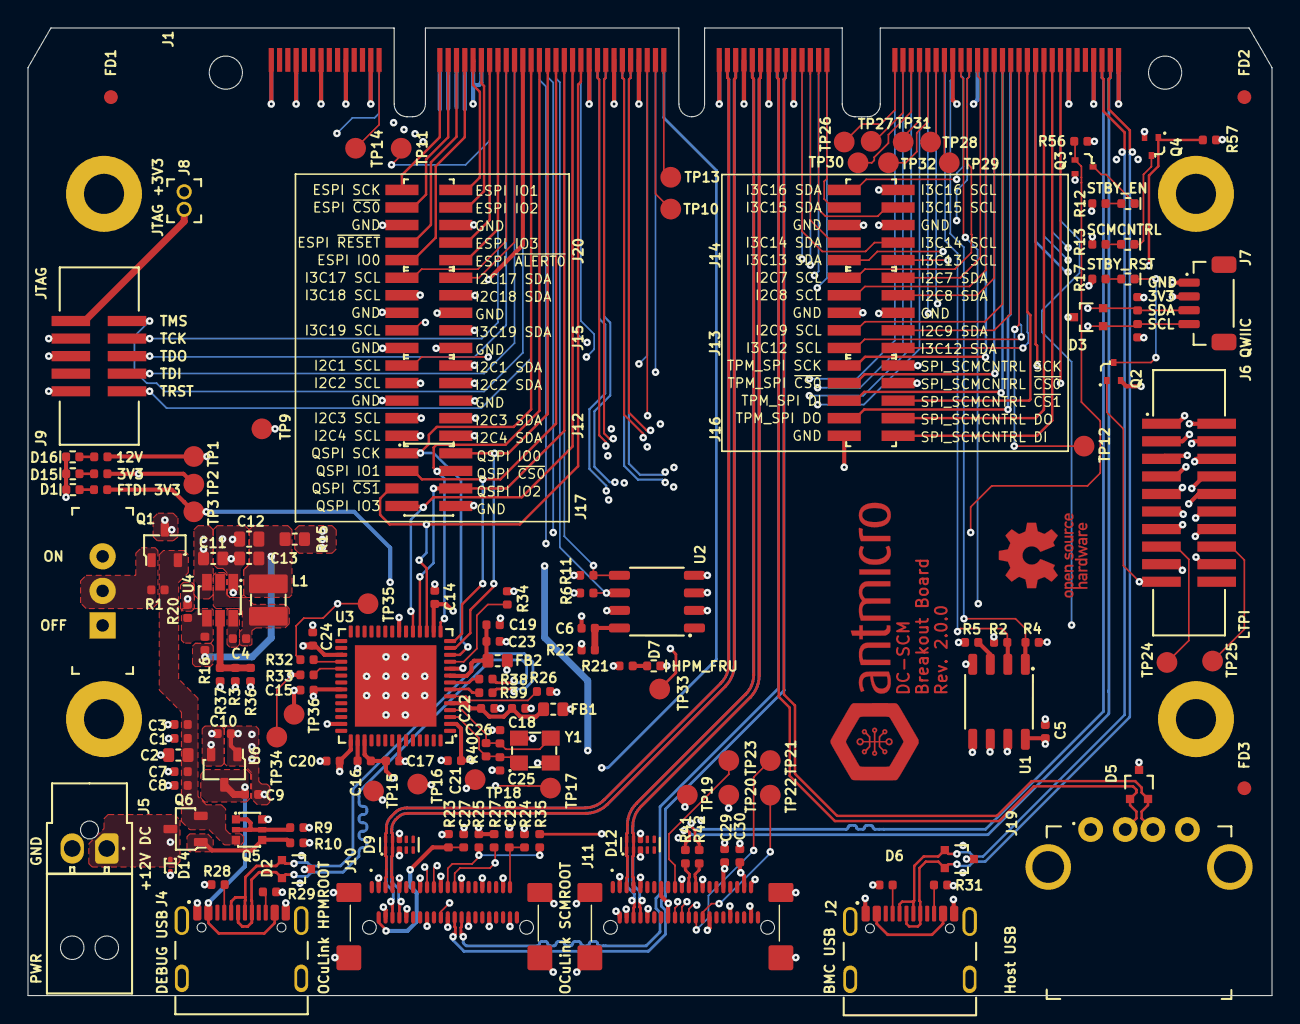
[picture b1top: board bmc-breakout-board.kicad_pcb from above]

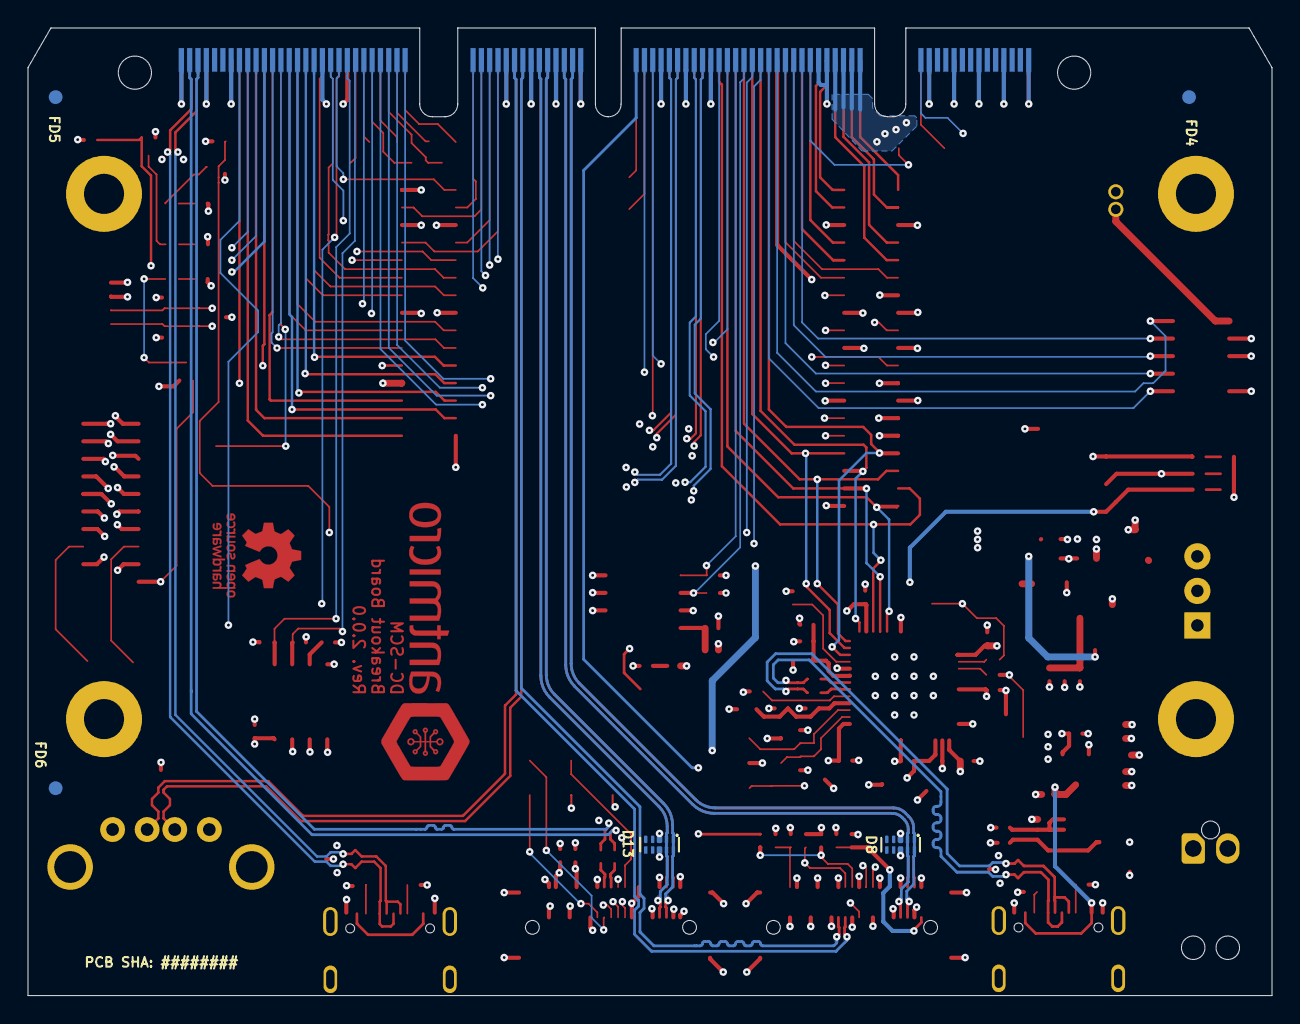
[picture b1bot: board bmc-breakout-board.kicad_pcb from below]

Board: 6 copper layers, 90.0 x 70.0 mm, 167 parts (5 on the bottom side), 172 nets.
